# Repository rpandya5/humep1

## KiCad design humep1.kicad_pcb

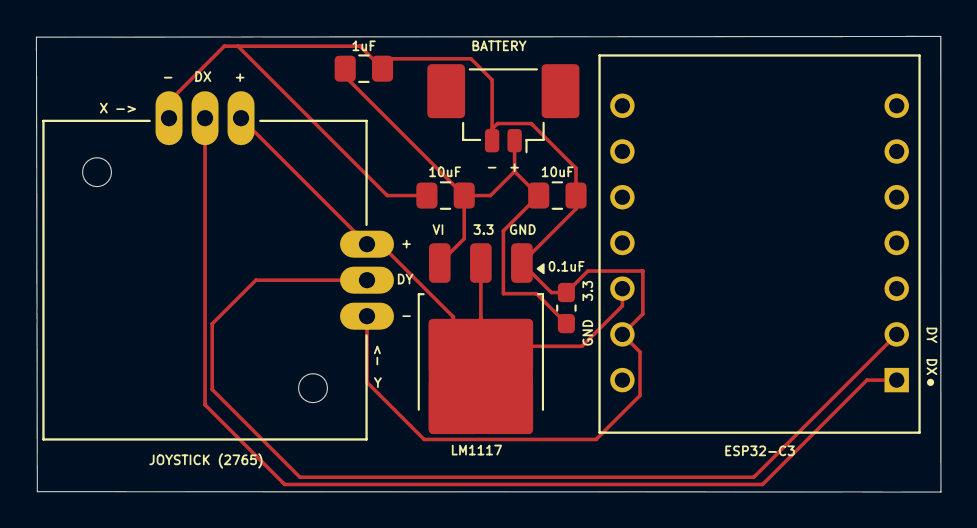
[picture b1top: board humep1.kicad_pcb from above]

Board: 2 copper layers, 50.2 x 25.3 mm, 8 parts (0 on the bottom side), 5 nets.

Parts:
0.1uF: 0.1uF; C_0603_1608Metric_Pad1.08x0.95mm_HandSolder
1uF: 1uF; C_0805_2012Metric_Pad1.18x1.45mm_HandSolder
10uF, 10uF#2: 10uF; C_0805_2012Metric_Pad1.18x1.45mm_HandSolder
BATTERY: BATTERY; Molex_PicoBlade_53398-0271_1x02-1MP_P1.25mm_Vertical
ESP32-C3: 113991054; MODULE_113991054
JOYSTICK (2765): 2765; SW_2765
U1: LM1117DT-3.3; TO-252-3_TabPin2

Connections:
/3.3V: ESP32-C3.12 (VCC_3V3), JOYSTICK (2765).X+, JOYSTICK (2765).Y+, U1.2 (VO)
/PWR: 0.1uF.1, 1uF.1, 10uF.1, 10uF#2.1, BATTERY.1 (+), U1.3 (VI)
/X: ESP32-C3.1 (D0), JOYSTICK (2765).X
/Y: ESP32-C3.2 (D1), JOYSTICK (2765).Y
GND: 0.1uF.2, 1uF.2, 10uF.2, 10uF#2.2, BATTERY.2 (-), ESP32-C3.13 (GND), JOYSTICK (2765).X-, JOYSTICK (2765).Y-, U1.1 (GND)

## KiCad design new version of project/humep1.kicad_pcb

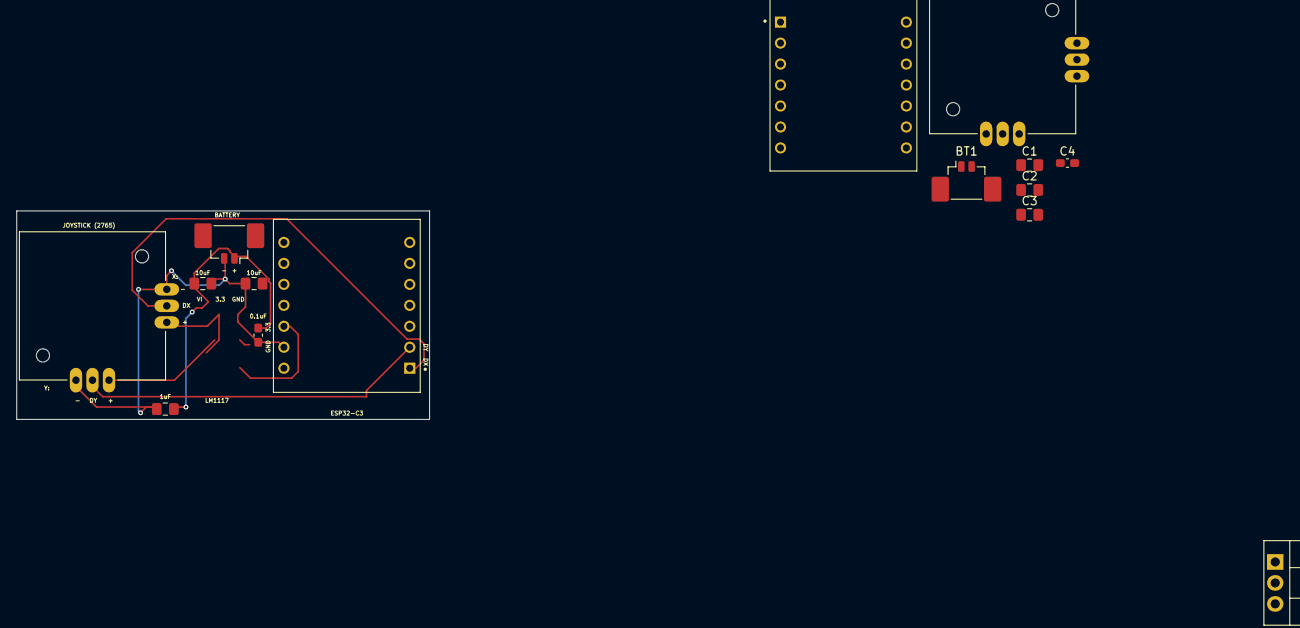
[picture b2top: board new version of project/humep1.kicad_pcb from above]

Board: 2 copper layers, 50.0 x 25.2 mm, 15 parts (0 on the bottom side), 5 nets.

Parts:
0.1uF: 0.1uF; C_0603_1608Metric_Pad1.08x0.95mm_HandSolder
1uF: 1uF; C_0805_2012Metric_Pad1.18x1.45mm_HandSolder
10uF, 10uF#2: 10uF; C_0805_2012Metric_Pad1.18x1.45mm_HandSolder
BATTERY: BATTERY; Molex_PicoBlade_53398-0271_1x02-1MP_P1.25mm_Vertical
BT1: BATTERY; Molex_PicoBlade_53398-0271_1x02-1MP_P1.25mm_Vertical
C1, C2: 10uF; C_0805_2012Metric_Pad1.18x1.45mm_HandSolder
C3: 1uF; C_0805_2012Metric_Pad1.18x1.45mm_HandSolder
C4: 0.1uF; C_0603_1608Metric_Pad1.08x0.95mm_HandSolder
ESP32-C3: 113991054; MODULE_113991054
JOYSTICK (2765): 2765; SW_2765
S1: 2765; SW_2765
U1: LM1117DT-3.3; TO-220-3_Vertical
U2: 113991054; MODULE_113991054

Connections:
/3.3V: ESP32-C3.12 (VCC_3V3), JOYSTICK (2765).X+, JOYSTICK (2765).Y+, S1.X+, S1.Y+, U1.2 (VO), U2.12 (VCC_3V3)
/PWR: 0.1uF.1, 1uF.1, 10uF.1, 10uF#2.1, BATTERY.1 (+), BT1.1 (+), C1.1, C2.1, C3.1, C4.1, U1.3 (VI)
/X: ESP32-C3.1 (D0), JOYSTICK (2765).X, S1.X, U2.1 (D0)
/Y: ESP32-C3.2 (D1), JOYSTICK (2765).Y, S1.Y, U2.2 (D1)
GND: 0.1uF.2, 1uF.2, 10uF.2, 10uF#2.2, BATTERY.2 (-), BT1.2 (-), C1.2, C2.2, C3.2, C4.2, ESP32-C3.13 (GND), JOYSTICK (2765).X-, JOYSTICK (2765).Y-, S1.X-, S1.Y-, U1.1 (GND), U2.13 (GND)

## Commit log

2024-05-13 completed schematic for all components except joystick
2024-05-19 completed footprint assignments
2024-05-20 formatted pcb
2024-05-20 updated schematic + completed pcb layout
2024-05-22 adapted into 1 layer pcb
2024-05-23 added stiffener, coverlays and exported
2024-05-27 updated files
